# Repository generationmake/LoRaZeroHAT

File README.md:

# LoRaZeroHAT
Raspberry Pi HAT with Ai-Thinker Ra-01 or Ra-02 LoRa module connected via SPI and an u-blox NEO-6M or NEO-M8N GNSS receiver connected to serial.

## PCB

### Top

### Bottom

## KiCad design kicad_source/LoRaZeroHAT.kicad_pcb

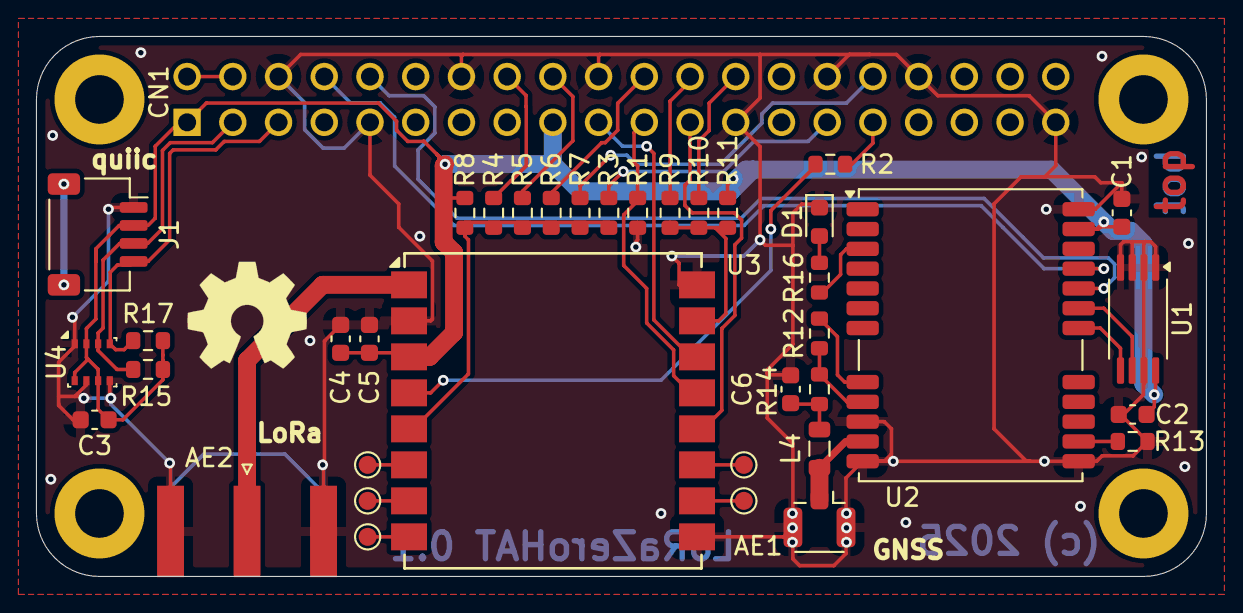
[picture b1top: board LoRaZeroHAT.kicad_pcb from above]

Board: 2 copper layers, 65.0 x 30.0 mm, 41 parts (1 on the bottom side), 36 nets.

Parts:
AE1: Antenna_Shield; U.FL_Hirose_U.FL-R-SMT-1_Vertical
AE2: Antenna_Shield; SMA_Amphenol_132289_EdgeMount
C1, C2, C3, C4, C6: 100 nF; C_0603_1608Metric
C5: 2.2 uF; C_0603_1608Metric
CN1: RASPI-IO; RASPI_ZERO_HAT_EDGE
D1: LED_Small; LED_0603_1608Metric
J1: SM04B-SRSS-TB; JST_SH_SM04B-SRSS-TB_1x04-1MP_P1.00mm_Horizontal
L1: Label; OSHW-Symbol_6.7x6mm_SilkScreen
L2: Label; generationmake_small_solder
L3: Label; generationmake_logo
L4: L; L_0805_2012Metric
R1, R8, R11, R15, R17: 10k; R_0603_1608Metric
R2, R6, R9, R12: 0R; R_0603_1608Metric
R3, R4, R5, R7, R10, R13: DNI; R_0603_1608Metric
R14: 10R; R_0603_1608Metric
R16: 1k; R_0603_1608Metric
TP1, TP2, TP3, TP4, TP5: TestPoint; TestPoint_Pad_D1.0mm
U1: 24LC32; TSSOP-8_4.4x3mm_P0.65mm
U2: NEO-M8N; ublox_NEO
U3: Ai-Thinker-Ra-01; Ai-Thinker-Ra-01-LoRa
U4: BME280; Bosch_LGA-8_2.5x2.5mm_P0.65mm_ClockwisePinNumbering

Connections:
+3.3V: C1.1, C2.1, C3.1, C4.1, C5.1, CN1.1 (3V3), CN1.17 (3V3), J1.2, R8.1, R11.1, R15.1, R17.1, U1.8 (VCC), U2.23 (VCC), U3.3 (VDD), U4.2 (CSB), U4.6 (VDDIO), U4.8 (VDD)
+5V: CN1.2 (5V0), CN1.4 (5V0)
/LoRa GNSS/D2_R: D1.2 (A), R16.2
/LoRa GNSS/LORA_ANTENNA: AE2.1 (A), U3.1 (ANT)
/LoRa GNSS/LORA_DIO1: TP1.1, U3.6 (DIO1)
/LoRa GNSS/LORA_DIO2: TP2.1, U3.7 (DIO2)
/LoRa GNSS/LORA_DIO3: TP3.1, U3.8 (DIO3)
/LoRa GNSS/LORA_DIO4: TP4.1, U3.10 (DIO4)
/LoRa GNSS/LORA_DIO5: TP5.1, U3.11 (DIO5)
/LoRa GNSS/NEO_ANTENNA: AE1.1 (A), L4.2, U2.11 (RF_IN)
/LoRa GNSS/NEO_I2C_SCL: U1.6 (SCL), U2.19 (SCL/SPI_CLK)
/LoRa GNSS/NEO_I2C_SDA: U1.5 (SDA), U2.18 (SDA/~SPI_CS)
/LoRa GNSS/NEO_RESET: R12.2, U2.8 (~RESET)
/LoRa GNSS/TIMEPULSE: R16.1, U2.3 (TIMEPULSE)
/LoRa GNSS/VCC_RF: R12.1, R14.1, U2.9 (VCC_RF)
/RaspberryPiZeroHAT/INTERRUPT_5: CN1.29 (BCM5), R3.1
/RaspberryPiZeroHAT/INTERRUPT_12: CN1.32 (BCM12/PWM0), R7.1
/RaspberryPiZeroHAT/INTERRUPT_23: CN1.16 (BCM23), R4.1
/RaspberryPiZeroHAT/INTERRUPT_24: CN1.18 (BCM24), R5.1
/RaspberryPiZeroHAT/INTERRUPT_25: CN1.22 (BCM25), R6.1
/RaspberryPiZeroHAT/LORA_RESET_R: CN1.31 (BCM6), R2.2
/RaspberryPiZeroHAT/SPI_CE0: CN1.24 (BCM8/CE0), R9.1
/RaspberryPiZeroHAT/SPI_CE1: CN1.26 (BCM9/CE1), R10.2
GND: AE1.2 (Shield), AE2.2 (Shield), C1.2, C2.2, C3.2, C4.2, C5.2, C6.2, CN1.6 (GND), CN1.9 (GND), CN1.14 (GND), CN1.20 (GND), CN1.25 (GND), CN1.30 (GND), CN1.34 (GND), CN1.39 (GND), D1.1 (K), J1.1, R1.2, R13.1, U1.1 (A0), U1.2 (A1), U1.3 (A2), U1.4 (GND), U1.7 (WP), U2.10 (GND), U2.12 (GND), U2.13 (GND), U2.24 (GND), U3.2 (GND), U3.9 (GND), U3.16 (GND), U4.1 (GND), U4.5 (SDO), U4.7 (GND)
I2C_SCL: CN1.5 (BCM3/SCL), J1.4, R17.2, U4.4 (SCK)
I2C_SDA: CN1.3 (BCM2/SDA), J1.3, R15.2, U4.3 (SDI)
LORA_CS: R9.2, R10.1, R11.2, U3.15 (~NSS)
LORA_INT: R3.2, R4.2, R5.2, R6.2, R7.2, R8.2, U3.5 (DIO0)
LORA_RESET: R2.1, U3.4 (~RESET)
unnamed: C6.1, L4.1, R14.2
unnamed: R13.2, U2.14 (LNA_EN)
SERIAL_RX: CN1.10 (BCM15/RXD), U2.20 (TXD/SPI_MISO)
SERIAL_TX: CN1.8 (BCM14/TXD), U2.21 (RXD/SPI_MOSI)
SPI_MISO: CN1.21 (BCM9/MISO), R1.1, U3.13 (MISO)
SPI_MOSI: CN1.19 (BCM10/MOSI), U3.14 (MOSI)
SPI_SCK: CN1.23 (BCM11/SCLK), U3.12 (SCK)

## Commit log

2025-09-02 copied kicad project together
2025-09-02 glued project together
2025-09-02 connected schematic to layout
2025-09-02 made first connections
2025-09-02 updated layout
2025-09-02 schaltplan neu annotiert
2025-09-02 updated DRC
2025-09-03 updated label
2025-09-04 added capacitor C6 on u-blox VCC_RF
2025-09-04 added schematic pdf
2025-09-04 added images

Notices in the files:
kicad_source/LoRaZeroHAT.kicad_pcb:
licensed under CERN-OHL-W v2
